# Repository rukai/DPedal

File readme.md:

# DPedal

A large foot controlled DPad.
It is built around a raspberry pi Pico and connects to your PC over usb to send user configurable HID keyboard and mouse events.

You can build your own from this design if you are comfortable with 3d printing, ordering PCB's from a manufacturer and some soldering.

To build your own dpedal follow [the instructions here](https://dpedal.com/build.html).

This repo contains the source for:

* The [firmware](https://github.com/rukai/DPedal/tree/main/dpedal_firmware)
* The [flashing tool](https://github.com/rukai/DPedal/tree/main/dpedal_flash)
* The [PCB](https://github.com/rukai/DPedal/tree/main/pcb)

The 3D printed parts are not in this repo, instead they are in [onshape](https://cad.onshape.com/documents/3322725aad79769314b0a0dc/w/7eb6c11c4e7989e30d759821/e/7eadfca9ff0dbd31823e3a21).

## Changes from [DPedal v2](https://github.com/rukai/dpedal_legacy)

* smaller height
  * foot is less raised off the ground
  * easier to take with you
* make buttons recessed into shell, protect them from snapping off
* 2 buttons instead of 4, I rarely use the buttons, I think having less buttons will make it easier to hit the right one.
* web-based flashing tool
* RP2040 instead of an STM32 chip

## rift?

Some of the crate names start with `rift_`, whats that about?
I'm currently splitting the internals out into a seperate project called RIFT (Rukai's Input Firmware Toolkit)

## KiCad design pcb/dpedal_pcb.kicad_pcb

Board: 2 copper layers, 7 parts (1 on the bottom side), 7 nets.

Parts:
A1: RaspberryPi_Pico; RaspberryPi_Pico_SMD_HandSolder
SW1, SW2, SW3, SW4, SW5, SW6: SW_Push; SW_Hotswap_Kailh_Choc_V1

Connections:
GND: A1.8 (GND), A1.13 (GND), A1.18 (GND), A1.23 (GND), A1.28 (GND), A1.33 (GND), A1.D2 (GND), SW1.2, SW2.2, SW3.1, SW4.1, SW5.1, SW6.1
button_left: A1.17 (GPIO13), SW1.1
button_right: A1.32 (GPIO27_ADC1), SW5.2
dpad_down: A1.21 (GPIO16), SW2.1
dpad_left: A1.22 (GPIO17), SW4.2
dpad_right: A1.29 (GPIO22), SW3.2
dpad_up: A1.31 (GPIO26_ADC0), SW6.2

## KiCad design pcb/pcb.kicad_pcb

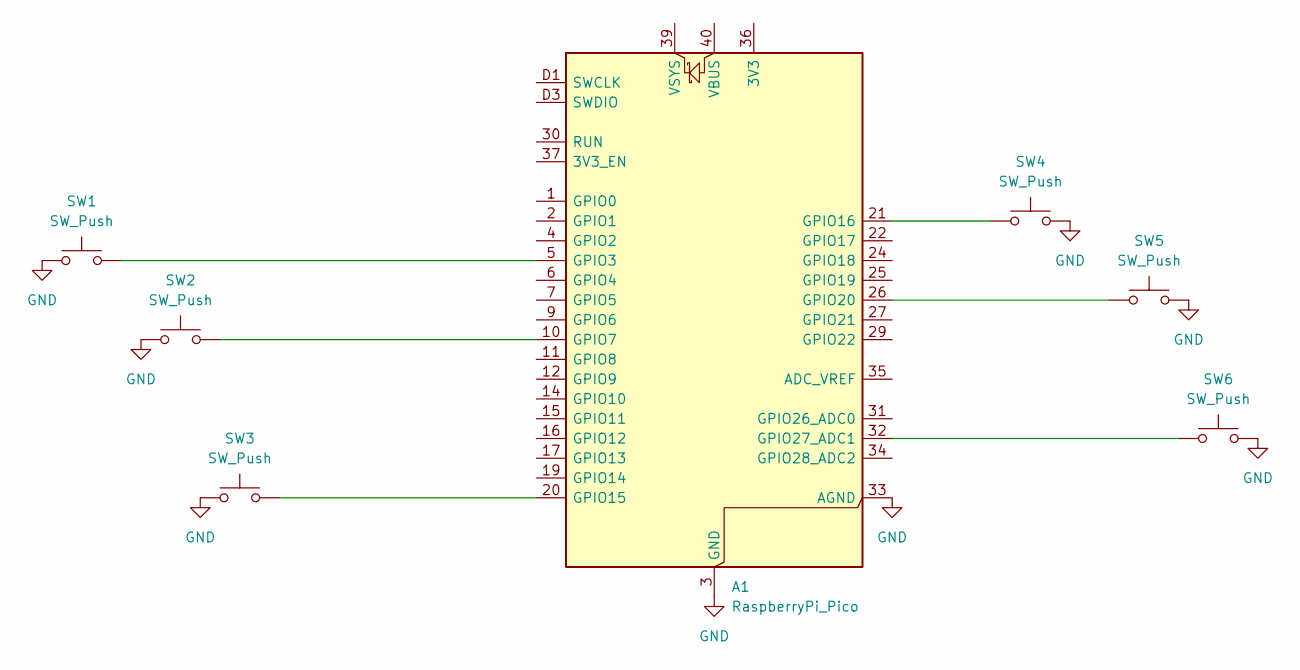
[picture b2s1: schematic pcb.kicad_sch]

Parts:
A1: RaspberryPi_Pico; RaspberryPi_Pico_SMD_HandSolder
SW1, SW2, SW3, SW4, SW5, SW6: SW_Push; SW_Hotswap_Kailh_Choc_V1

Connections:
GND: A1.3 (GND), A1.8 (GND), A1.13 (GND), A1.18 (GND), A1.23 (GND), A1.28 (GND), A1.33 (AGND), A1.38 (GND), A1.D2 (GND), SW1.1, SW2.1, SW3.1, SW4.2, SW5.2, SW6.2
unnamed: A1.5 (GPIO3), SW1.2
unnamed: A1.10 (GPIO7), SW2.2
unnamed: A1.20 (GPIO15), SW3.2
unnamed: A1.21 (GPIO16), SW4.1
unnamed: A1.26 (GPIO20), SW5.1
unnamed: A1.32 (GPIO27_ADC1), SW6.1

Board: 2 copper layers, 7 parts (1 on the bottom side), 7 nets.

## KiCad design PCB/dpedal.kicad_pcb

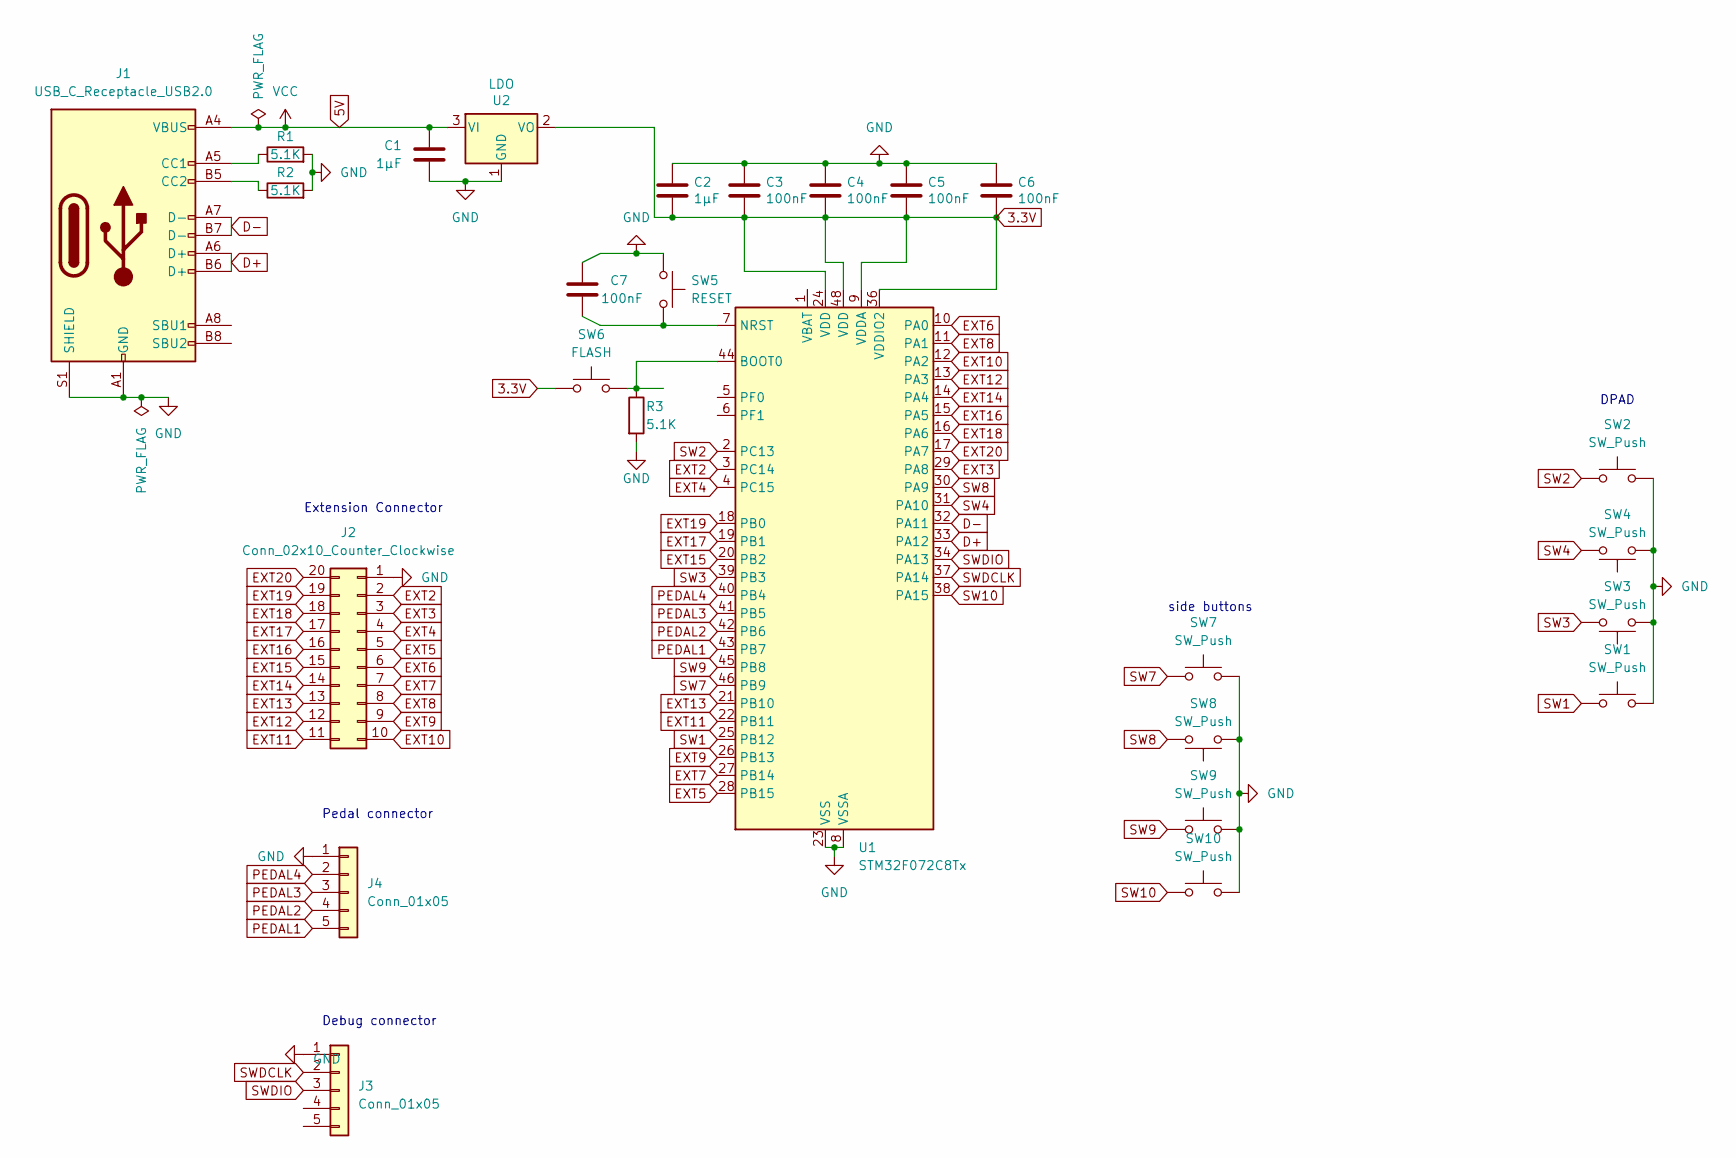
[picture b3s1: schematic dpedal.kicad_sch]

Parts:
C1, C2: 1µF; C_0402_1005Metric; LCSC C52923
C3, C4, C5, C6: 100nF; C_0402_1005Metric; LCSC C60474
C7: 100nF; C_0402_1005Metric
J1: USB_C_Receptacle_USB2.0; USB_C_Receptacle_HRO_TYPE-C-31-M-12; JLCPCB Part # C165948
J2: Conn_02x10_Counter_Clockwise; IDC-Header_2x10_P2.54mm_Horizontal; JLCPCB Part # C132444
J3: Conn_01x05; PinSocket_1x05_P2.54mm_Vertical
J4: Conn_01x05; PinSocket_1x05_P2.54mm_Horizontal; JLCPCB Part # C124405
R1, R2, R3: 5.1K; R_0402_1005Metric; JLCPCB Part # C25905
SW1, SW2, SW3, SW4, SW7, SW8, SW9, SW10: SW_Push; SW_Hotswap_Kailh_MX
SW5: RESET; SW_SPST_CK_RS282G05A3; JLCPCB Part # C5117870
SW6: FLASH; SW_SPST_CK_RS282G05A3; JLCPCB Part # C5117870
U1: STM32F072C8Tx; LQFP-48_7x7mm_P0.5mm; JLCPCB Part # C80488
U2: LDO; SOT-23-3; LCSC C347376

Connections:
3.3V: C2.2, C3.2, C4.2, C5.2, C6.2, SW6.1, U1.9 (VDDA), U1.24 (VDD), U1.36 (VDDIO2), U1.48 (VDD), U2.2 (VO)
5V: C1.2, J1.A4 (VBUS), J1.A9 (VBUS), J1.B4 (VBUS), J1.B9 (VBUS), U2.3 (VI)
D+: J1.A6 (D+), J1.B6 (D+), U1.33 (PA12)
D-: J1.A7 (D-), J1.B7 (D-), U1.32 (PA11)
EXT2: J2.2, U1.3 (PC14)
EXT3: J2.3, U1.29 (PA8)
EXT4: J2.4, U1.4 (PC15)
EXT5: J2.5, U1.28 (PB15)
EXT6: J2.6, U1.10 (PA0)
EXT7: J2.7, U1.27 (PB14)
EXT8: J2.8, U1.11 (PA1)
EXT9: J2.9, U1.26 (PB13)
EXT10: J2.10, U1.12 (PA2)
EXT11: J2.11, U1.22 (PB11)
EXT12: J2.12, U1.13 (PA3)
EXT13: J2.13, U1.21 (PB10)
EXT14: J2.14, U1.14 (PA4)
EXT15: J2.15, U1.20 (PB2)
EXT16: J2.16, U1.15 (PA5)
EXT17: J2.17, U1.19 (PB1)
EXT18: J2.18, U1.16 (PA6)
EXT19: J2.19, U1.18 (PB0)
EXT20: J2.20, U1.17 (PA7)
GND: C1.1, C2.1, C3.1, C4.1, C5.1, C6.1, C7.1, J1.A1 (GND), J1.A12 (GND), J1.B1 (GND), J1.B12 (GND), J1.S1 (SHIELD), J2.1, J3.1, J4.1, R1.2, R2.2, R3.2, SW1.2, SW2.2, SW3.1, SW4.1, SW5.1, SW7.2, SW8.1, SW9.2, SW10.2, U1.8 (VSSA), U1.23 (VSS), U1.35 (VSS), U1.47 (VSS), U2.1 (GND)
unnamed: J1.A5 (CC1), R1.1
unnamed: J1.B5 (CC2), R2.1
unnamed: R3.1, SW6.2, U1.44 (BOOT0)
unnamed: C7.2, SW5.2, U1.7 (NRST)
PEDAL1: J4.5, U1.43 (PB7)
PEDAL2: J4.4, U1.42 (PB6)
PEDAL3: J4.3, U1.41 (PB5)
PEDAL4: J4.2, U1.40 (PB4)
SW1: SW1.1, U1.25 (PB12)
SW2: SW2.1, U1.2 (PC13)
SW3: SW3.2, U1.39 (PB3)
SW4: SW4.2, U1.31 (PA10)
SW7: SW7.1, U1.46 (PB9)
SW8: SW8.2, U1.30 (PA9)
SW9: SW9.1, U1.45 (PB8)
SW10: SW10.1, U1.38 (PA15)
SWDCLK: J3.2, U1.37 (PA14)
SWDIO: J3.3, U1.34 (PA13)

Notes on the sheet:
Extension Connector
Debug connector
DPAD
Pedal connector
side buttons

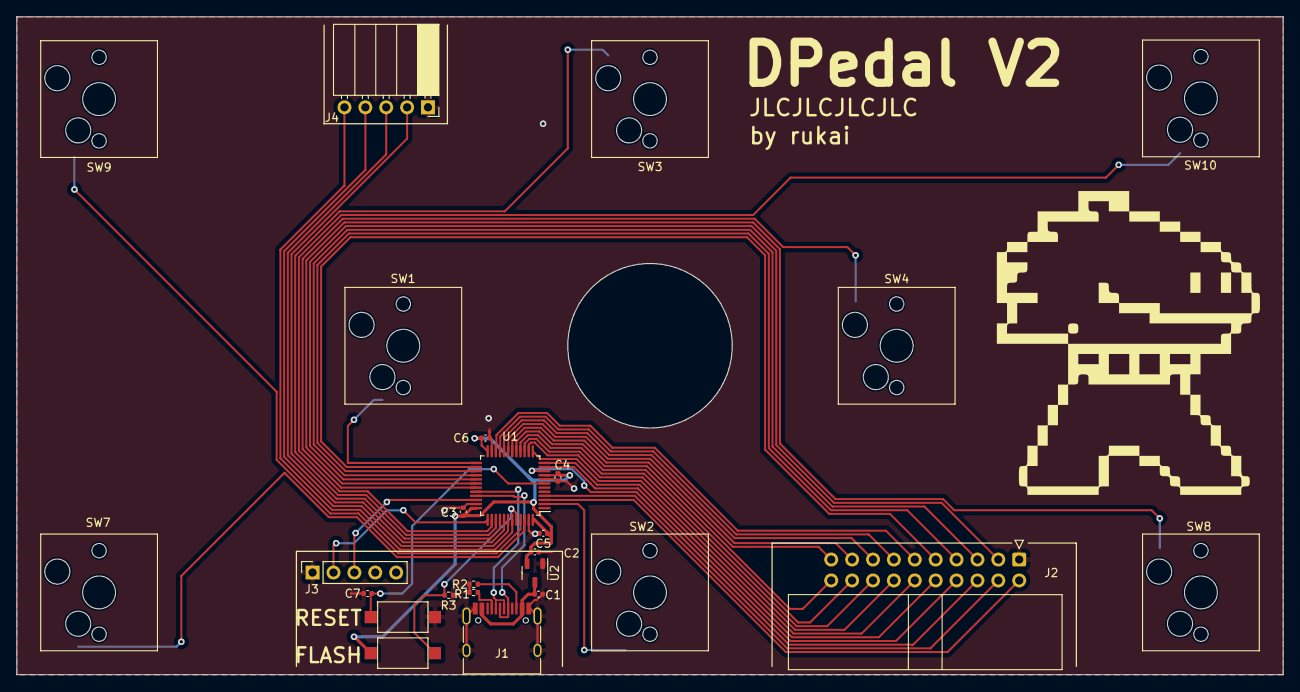
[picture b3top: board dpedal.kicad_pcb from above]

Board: 2 copper layers, 154.0 x 80.0 mm, 26 parts (0 on the bottom side), 42 nets.

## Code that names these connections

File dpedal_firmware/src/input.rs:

use core::ops::ControlFlow;
use dpedal_config::{DpedalInput, Meta};
use embassy_rp::gpio::{AnyPin, Input, Pin, Pull};
use embassy_rp::{Peri, PeripheralType};
use embassy_sync::{blocking_mutex::raw::CriticalSectionRawMutex, mutex::Mutex};
use embassy_time::Timer;
use rift_config::Profile;
use rift_firmware::config::{CONFIG_UPDATED, ConfigFlash};
use rift_firmware::mapping_state::{MappingState, State};
use static_cell::StaticCell;

static CURRENT_PROFILE: StaticCell<Profile<DpedalInput>> = StaticCell::new();

pub struct Inputs {
    pins: [Option<Peri<'static, AnyPin>>; 30],
    config_flash: &'static Mutex<CriticalSectionRawMutex, ConfigFlash>,
}

impl Inputs {
    pub fn new(
        config_flash: &'static Mutex<CriticalSectionRawMutex, ConfigFlash>,
        pins: [Option<Peri<'static, AnyPin>>; 30],
    ) -> Self {
        Inputs { pins, config_flash }
    }

    pub async fn process(&mut self) {
        let mut rx = CONFIG_UPDATED.receiver().unwrap();

        let mut button_left_pin = 13;
        let mut button_right_pin = 27;
        let mut dpad_up_pin = 26;
        let mut dpad_down_pin = 16;
        let mut dpad_left_pin = 17;
        let mut dpad_right_pin = 22;

        // Load initial config
        let meta: Meta = self.config_flash.lock().await.load_meta().await;
        let current_profile = {
            // TODO: currently handles config with 0 profiles by loading the default profile which has mappings in it.
            //       this is unintuitive and should be changed.
            let profile = self.config_flash.lock().await.load_profile(0).await;
            CURRENT_PROFILE.init(profile)
        };

        // Apply pin remappings from meta (set once; remappings not editable via web configurator)
        for remapping in &meta.pin_remappings {
            match remapping.input {
                DpedalInput::DpadUp => dpad_up_pin = remapping.pin as usize,
                DpedalInput::DpadDown => dpad_down_pin = remapping.pin as usize,
                DpedalInput::DpadLeft => dpad_left_pin = remapping.pin as usize,
                DpedalInput::DpadRight => dpad_right_pin = remapping.pin as usize,
                DpedalInput::ButtonLeft => button_left_pin = remapping.pin as usize,
                DpedalInput::ButtonRight => button_right_pin = remapping.pin as usize,
            }
        }

        let button_left = input(self.pins[button_left_pin].take().unwrap());
        let button_right = input(self.pins[button_right_pin].take().unwrap());
        let dpad_up = input(self.pins[dpad_up_pin].take().unwrap());
        let dpad_down = input(self.pins[dpad_down_pin].take().unwrap());
        let dpad_left = input(self.pins[dpad_left_pin].take().unwrap());
        let dpad_right = input(self.pins[dpad_right_pin].take().unwrap());

        let mut state = State::new();
        let mut loaded_profile_index: u8 = 0;

        'main_loop: loop {
            // Detect config updates (ReloadConfig from web configurator); reset to profile 0
            if rx.try_changed().is_some() {
                state = State::new();
                loaded_profile_index = u8::MAX; // force reload via the block below
            }

            // Load new profile from flash when current profile changed
            if state.current_profile != loaded_profile_index {
                *current_profile = self
                    .config_flash
                    .lock()
                    .await
                    .load_profile(state.current_profile)
                    .await;
                loaded_profile_index = state.current_profile;
                state.mapping_states.clear();
            }

            let input_state = DpedalInputState {
                button_left: button_left.is_low(),
                button_right: button_right.is_low(),
                dpad_up: dpad_up.is_low(),
                dpad_down: dpad_down.is_low(),
                dpad_left: dpad_left.is_low(),
                dpad_right: dpad_right.is_low(),
            };

            // Restore mapping state to full length in case it was cleared earlier
            while current_profile.mappings.len() > state.mapping_states.len() {
                if state.mapping_states.push(MappingState::new()).is_err() {
                    defmt::panic!("mapping state overflow");
                }
            }

            for (i, mapping) in current_profile.mappings.iter().enumerate() {
                let all_pressed = input_state.is_all_pressed(&mapping.input_set);
                state.mapping_states[i] = match state.mapping_states[i]
                    .process(mapping, all_pressed, &mut state)
                    .await
                {
                    ControlFlow::Continue(ms) => ms,
                    ControlFlow::Break(()) => continue 'main_loop,
                };
            }

            Timer::after_millis(1).await;
        }
    }
}

struct DpedalInputState {
    button_left: bool,
    button_right: bool,
    dpad_up: bool,
    dpad_down: bool,
    dpad_left: bool,
    dpad_right: bool,
}

impl DpedalInputState {
    fn is_all_pressed(&self, check: &[DpedalInput]) -> bool {
        // Disable the mapping when the inputs are entirely empty
        // It is an obvious configuration mistake and having it constantly trigger the input would be very annoying
        if check.is_empty() {
            return false;
        }

        for input in check {
            let pressed = match input {
                DpedalInput::DpadUp => self.dpad_up,
                DpedalInput::DpadDown => self.dpad_down,
                DpedalInput::DpadLeft => self.dpad_left,
                DpedalInput::DpadRight => self.dpad_right,
                DpedalInput::ButtonLeft => self.button_left,
                DpedalInput::ButtonRight => self.button_right,
            };

            if !pressed {
                return false;
            }
        }
        true
    }
}

// TODO: become Input::new
fn input<T: PeripheralType + Pin>(pin: Peri<'static, T>) -> Input<'static> {
    let mut pin = Input::new(pin, Pull::Up);
    pin.set_schmitt(true);
    pin
}

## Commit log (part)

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2022-12-27 progress
2022-12-29 Getting ready to order
2022-12-29 Ordered design
2022-12-29 move kicad to subfolder
2022-12-29 readme improvements
2022-12-30 Initial firmware implementation
2023-01-09 Initial flash readme
2023-01-10 Fix matrix, we are using direct pin connections instead of a proper matrix so we need to use DirectPinMatrix instead of Matrix
2023-01-10 Add CI
2023-01-22 Add initial flasher tool
2023-01-23 ensure firmware is built at flasher compile time
2023-01-26 Initial work towards reading/writing device config
2023-01-27 more printing instructions
2023-01-27 Update rust version
2023-01-27 succesfully load a single byte from the config memory
2023-01-28 Succesfully pass keycodes from the flasher to the firmware
2023-01-29 Implement config file
2023-01-29 miettify
2023-01-29 add image to readme
2023-01-31 Fix build.rs rerun detection
2023-02-04 V1 parts link
2023-02-05 PCB v2
2023-03-06 PCB v2 More
2023-03-06 Convert to kicad 7.0
2023-03-06 Update symbols/footprints
2023-03-07 Fix 3d models for kicad 7
2023-03-07 pcb fixes
2023-03-10 rename dpedal_flasher to dpedalflash
2023-03-11 simplify CLI UX
2023-03-11 PCB fix drc errors + change pedal headers to 2.54mm
2023-03-11 Move reset and flash buttons to bottom of board
2023-03-11 Move debug port down
2023-03-11 Better align components to shell holes
2023-03-12 Finalize PCB BOM
2023-03-12 Swap out cortex debug connector for custom 2.54 pinout (2.54 will be much easier to hand solder)
2023-03-14 more final pcb cleanup
2023-03-23 Implement firmware for dpedal v2
2023-03-23 Add cargo-dist
2023-03-23 release 0.1.1
2023-03-23 Document flashing precompiled firmware
2023-03-31 Improve print instructions + add list of keycodes to example config
2023-04-01 Improve keymap names
2023-04-01 Update photo
2023-04-01 Fixes to default config
2023-11-18 Upgrade dependencies and rust version
2023-11-18 Update deps major versions
2023-11-19 Release 0.1.1 (#1)
2023-11-19 Release v0.1.2
2023-11-19 Release v0.1.2 (#2)
2023-11-24 Port to usbd_human_interface_device
2023-11-24 Port to usbd_human_interface_device (#3)
2023-11-25 Use zbindeps (moved to nightly)
2023-11-25 Use zbindeps (moved to nightly) (#4)
2024-04-09 Update rust nightly
2024-04-09 Update rust nightly (#5)
2024-04-11 Minor readme fix
    prusa slicer only has one 0.1mm layer height profile and is not called
    QUALITY
2024-04-11 Minor readme fix (#6)
    prusa slicer only has one 0.1mm layer height profile and is not called
    QUALITY
2025-01-02 Update to latest rust nightly
2025-01-02 Update deps
2025-01-02 Update firmware deps
2025-01-02 Update deps (#7)
    * Update to latest rust nightly
    * Update deps
    * Update firmware deps
2025-01-05 Update to rust 2024
2025-01-05 Update to rust 2024 (#8)
2025-07-18 Update rust version (#9)
2025-07-30 disable broken fillet
2025-07-30 spheres can now be unionized!
2025-08-22 mess around with dpedal site idea
2025-08-23 Background numbers
2025-10-06 Update rust
2025-10-06 Update rust (#10)
2025-10-06 Add support for mouse inputs
2025-10-06 Add mouse clicks
2025-10-06 Mouse scroll + click support (#11)
    * Add support for mouse inputs
    * Add mouse clicks
2025-10-07 Release 0.1.3
2025-10-07 Release 0.1.3 (#12)
2025-10-07 Fix release workflow
2025-10-07 Fix release workflow (#13)
2025-10-07 Test cargo build in CI and disable mac os CI builds
2025-10-07 Test cargo build in CI and disable mac os CI builds (#14)
2025-11-03 get zoo model compiling again
2025-11-06 cleanup config
2025-11-06 build instructions
2025-11-08 Move kdl_config into its own repo
2025-11-09 Rewrite with embassy
2025-11-09 Implement hacky bindeps at home to use stable rust
2025-11-09 fix pan+move
2025-11-15 add PCB
2025-11-16 rename kicad files
2025-11-16 board redesign
2025-11-16 add step file to kicad export script
2025-11-17 fix erc/drc
2025-11-17 move pico pads out 0.5mm from center.
2025-11-17 tweak pcb
2025-11-18 silkscreen
2025-11-20 initial build page
2025-11-22 move pcb section
2025-11-23 Add generator step for website
2025-11-23 more docs
2025-11-23 Setup CI
2025-11-23 remove dist.toml
2025-11-28 Add lint GA workflow
2025-11-28 Add stub for config web app
2025-11-29 Serve gzip
2025-11-29 Build wasm for website
2025-11-29 split assets into media and assets folder
2025-11-29 Add basic input/output table generation
2025-11-30 Attempt to connect wasm app to device (it doesnt work yet)
2025-11-30 Achieve basic communication
2025-12-04 Send simple postcard message
2025-12-04 generate input/output table from device config
2025-12-06 Improve webusb protocol
2025-12-06 Fix table headers
2025-12-06 Make config format more flexible
2025-12-06 cleanup UI a little
2025-12-06 Refactor usb protocol into Device type
2025-12-07 Implement save button
2025-12-07 quickly hack in pin remapping
2025-12-08 flasher custom config path
2025-12-08 soldering docs
2025-12-13 fix CI
2025-12-13 progress on writing config from webpage
2025-12-13 firmware writes config to flash
2025-12-14 build page improvement
2025-12-15 remove unsafe from config loading
2025-12-15 Implement writing firmware to flash
2025-12-15 move main task into function
2025-12-15 reload config after writing to flash
2025-12-15 refactor input task
2025-12-15 tweak table color in dark mode
2025-12-16 Update rust and minor error handling improvement
2025-12-18 Fix webusb on windows
2025-12-18 windows build
2025-12-18 Release 0.0.2
2025-12-18 Fix deadlink
2025-12-19 Refactor config to better support multiple output types
2025-12-19 Release 0.0.3
2025-12-21 Allow flashing tool to flash 0's to config for testing purposes
2025-12-21 Initial plan
2025-12-21 add web alert for invalid config
2025-12-21 refactor input config to avoid manual definition and allow subfields
2025-12-22 Implement mouse clicking
2025-12-22 Implement color + name config
2025-12-22 Include device nickname in usb product field
2025-12-22 Release v0.0.4
2025-12-22 Improve input styling
2025-12-23 Fix mapping multiple inputs to the same output
2025-12-24 Add more error handling
2025-12-24 Add save animation
2025-12-24 Lock the device during request/response
2025-12-24 Add missing keyboard inputs
2025-12-24 Release 0.0.5
2025-12-29 Fix mouse up/down flipped
2026-01-01 Add discord to homepage
2026-01-01 Add embed metadata
2026-01-01 build instructions improvements
2026-01-01 add more build instructions
2026-01-01 Add scroll test page
2026-01-02 photos for flashing section
2026-01-03 Link to github repo on landing page
2026-02-09 Cleanup flash offsets
2026-02-14 Fix color parsing for colors < 0x100000
2026-02-14 Fix color parsing for colors < 0x100000 (#3)
2026-03-01 Bump number of profiles from 2 -> 5 (profiles still not usable yet)
2026-03-01 Bump number of profiles from 2 -> 5 (profiles still not usable yet) (#4)
2026-03-02 Add profile support to DPedal firmware
    Also allow web configurator to configure a "SetProfile" button.
    This is not yet enough for profiles to be useful though.
2026-03-02 Add profile support to DPedal firmware (#5)
    Also allow web configurator to configure a "SetProfile" button.
    This is not yet enough for profiles to be useful though.
2026-03-05 various refactors/cleanups
2026-03-05 various refactors/cleanups (#6)
2026-03-06 further refactor/cleanup
2026-03-06 further refactor/cleanup (#7)
2026-03-06 web app profile support
2026-03-06 web app - Add profile button
2026-03-06 web app - Add remove profile button
2026-03-06 improve UX
2026-03-06 web app - fixup spacing
2026-03-06 Web app - add multiple profile support (#8)
2026-03-06 Dont clone config in usb.rs
2026-03-06 add CONFIG_UPDATED
2026-03-06 Fix config badness (#9)
    * Dont clone config in usb.rs
    * add CONFIG_UPDATED
2026-03-06 web config - Allow selecting dpedal input
2026-03-06 web config - allow adding/removing input dropdowns
2026-03-06 web config - input chord configuration (#10)
    * web config - Allow selecting dpedal input
    * web config - allow adding/removing input dropdowns
2026-03-07 constants cleanup
2026-03-07 reduce casting noise
2026-03-07 Cleanup casting (#11)
    * constants cleanup
    * reduce casting noise
2026-03-07 web config - allow add/remove of pc inputs
2026-03-07 web config - allow add/remove of pc inputs (#12)
2026-03-07 web config refactor - Add AddRemoveButtons abstraction
2026-03-07 web config refactor - Add AddRemoveButtons abstraction (#13)
2026-03-07 web config - add buttons to add/remove mapping rows
2026-03-07 web config - add buttons to add/remove mapping rows (#14)
2026-03-07 UX tweaks
2026-03-07 UX tweaks (#15)
2026-03-07 More UX tweaks
2026-03-07 More UX tweaks (#16)
2026-03-07 Color improvements
2026-03-08 table wip
2026-03-08 Color improvements - and other fun stuff (#17)
    * Color improvements
    * table wip
2026-03-08 Release v0.0.6 (#18)
2026-03-08 Move web app specific CSS into web app
2026-03-08 Move web app specific CSS into web app (#19)
2026-03-08 Two column layout for large screens
2026-03-08 Add device type field
2026-03-08 Two column layout for large screens (#20)
    * Two column layout for large screens
    * Add device type field
2026-03-08 tooltips
2026-03-08 tooltips (#21)
2026-03-08 Support reopening previously opened devices
2026-03-08 Support reopening previously opened devices (#22)
2026-03-12 Refactor config to support new mapping modes
2026-03-12 Refactor config to support new mapping modes (#24)
2026-03-12 Fix modifiers (shift, ctrl etc.)
2026-03-12 Fix modifiers (shift, ctrl etc.) (#25)
2026-03-13 Add mode column
2026-03-13 Add mode column (#26)
2026-03-14 Implement mapping modes in firmware
2026-03-14 refactor
2026-03-14 Implement mapping modes in firmware (#27)
2026-03-14 web config: improve mode column
2026-03-14 simplify some names
2026-03-14 web config: improve mode column (#28)
    * web config: improve mode column
    * simplify some names
2026-03-14 Add profile examples
2026-03-14 Add profile examples (#29)
2026-03-15 Release v0.0.7
2026-03-15 Release v0.0.7 (#30)
2026-03-15 Fix SetProfile retriggering an equivalent input in the new profile
2026-03-15 Fix SetProfile retriggering an equivalent input in the new profile (#31)
2026-03-18 Add website address to PCB silkscreen
2026-03-19 Add website address to PCB silkscreen (#32)
2026-03-19 Fix image rendering in build.html
2026-03-19 Fix image rendering in build.html (#33)
2026-03-20 Fix landing page horizontal scroll
2026-03-20 Fix landing page horizontal scroll (#35)
2026-03-21 Swap arrayvec->heapless and rkyv->postcard
2026-03-21 Swap arrayvec->heapless and rkyv->postcard (#36)
2026-03-21 Add wear leveling via sequentail-storage
2026-03-21 Reallocate flash
2026-03-21 fix dpedal_flash
2026-03-22 Add wear leveling via sequential-storage (#37)
    * Add wear leveling via sequentail-storage
    * Reallocate flash
    * fix dpedal_flash
    * refactor nor flash abstraction
2026-03-22 Fix flash progress indicator
2026-03-22 Fix flash progress indicator (#38)
2026-03-22 reduce config ram usage
2026-03-22 reduce config ram usage (#39)
2026-03-22 Release v0.0.8
2026-03-22 Release v0.0.8 (#40)
2026-03-22 update docs for V0.12 printed parts
2026-04-03 Update docs for v0.13 parts
2026-04-04 update docs for V0.12 printed parts (#34)
    * update docs for V0.12 printed parts
    * Update docs for v0.13 parts
2026-04-04 Release v0.0.9 - (for hardware changes external to this repo)
2026-04-04 Release v0.0.9 - (for hardware changes external to this repo) (#41)
2026-04-04 Fix outdated images on website/repo
2026-04-04 Fix outdated images on website/repo (#42)
2026-04-18 Document keycap/dpad bundled part
2026-04-18 Document keycap/dpad bundled part (#43)
2026-04-18 Update to rust 1.95 (#44)
2026-05-03 Add config tests
2026-05-03 Add config tests (#45)
2026-05-03 Refactor diagnostics to use builder API
2026-05-03 Refactor diagnostics to use builder API (#46)
2026-05-03 Add GA workflow to run tests
2026-05-03 Add GA workflow to run tests (#47)
2026-05-03 Mappings parse as arguments
2026-05-03 Mappings parse as arguments (#48)
2026-05-03 dpedal_flash: add mutiple input/output configurations
2026-05-03 attempt1
2026-05-03 dpedal_flash: add multi input output support (#49)
2026-05-03 Release dpedal v0.0.10
2026-05-03 Release dpedal v0.0.10 (#50)
2026-05-04 replace flakey kicad ppa with docker image
2026-05-04 replace flakey kicad ppa with docker image (#51)
2026-06-08 rift
2026-06-08 more
